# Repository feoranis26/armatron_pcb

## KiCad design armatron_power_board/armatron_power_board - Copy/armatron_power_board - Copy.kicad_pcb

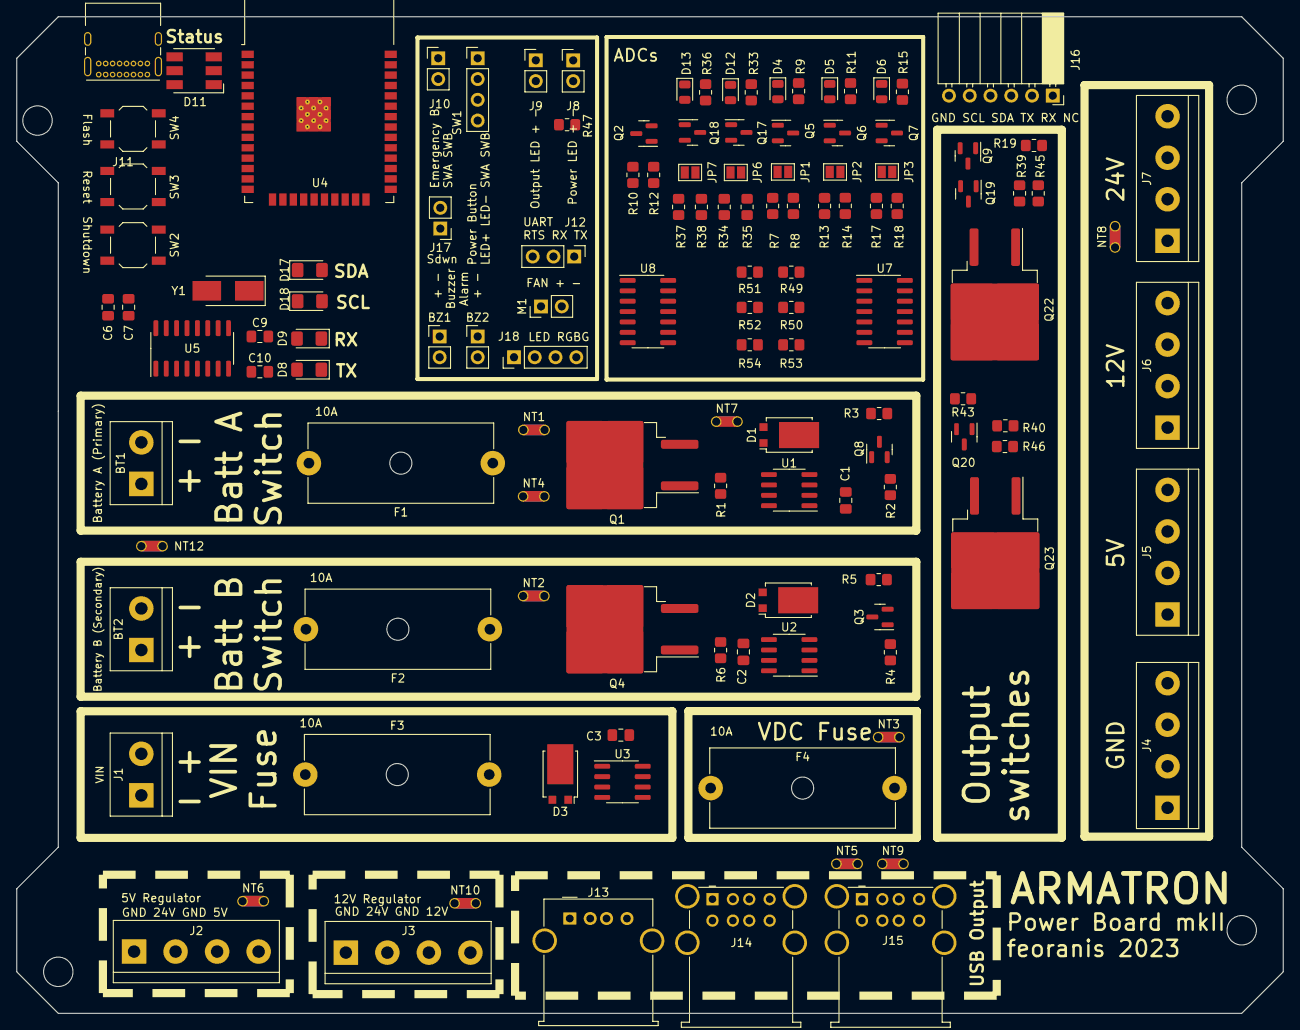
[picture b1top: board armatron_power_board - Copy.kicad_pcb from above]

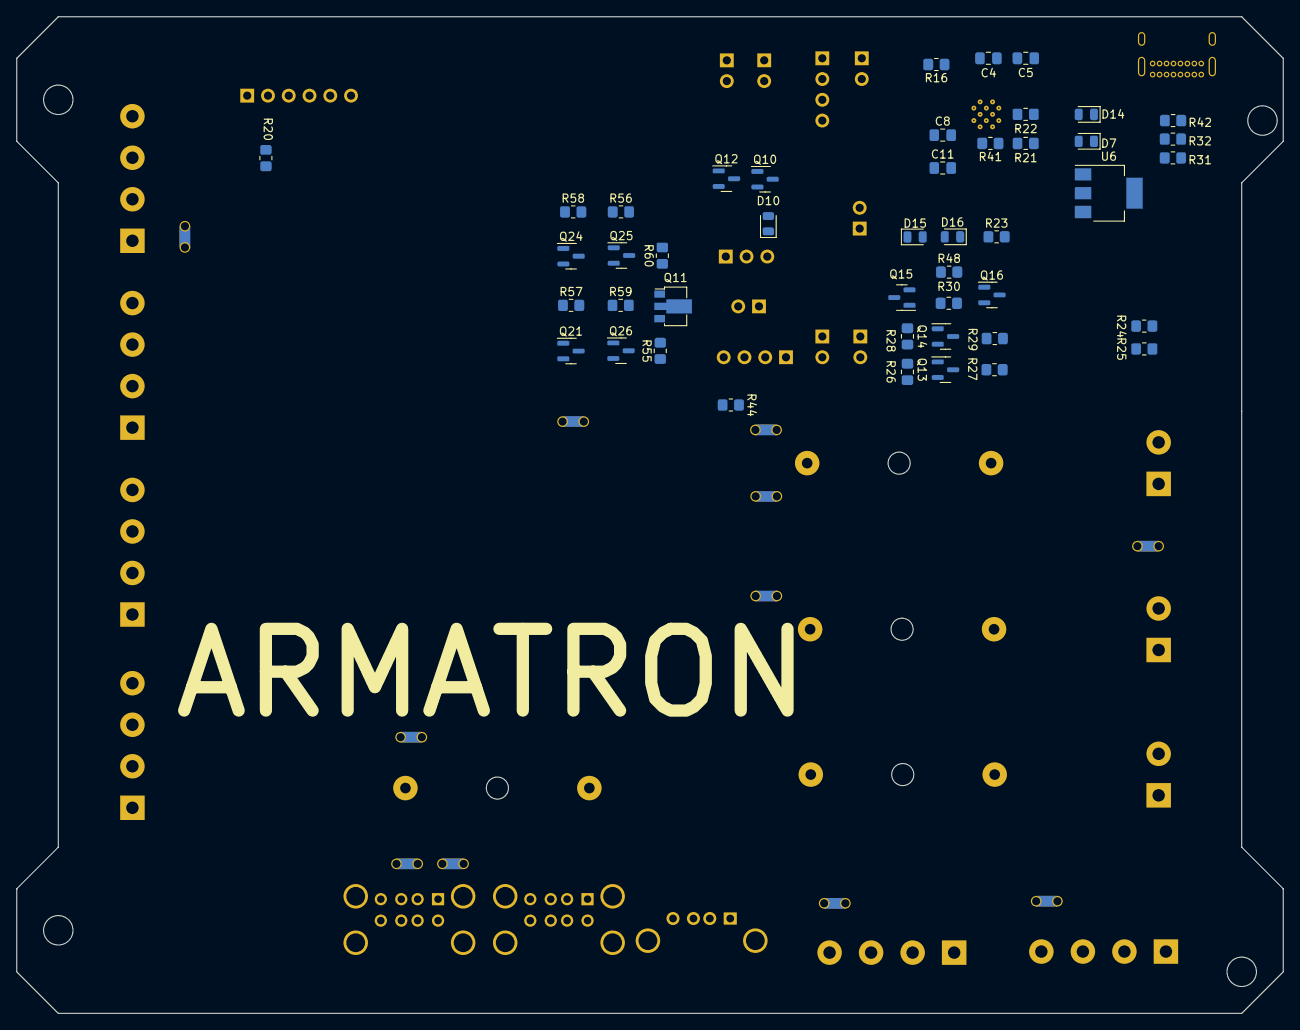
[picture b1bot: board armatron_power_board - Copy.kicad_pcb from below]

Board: 2 copper layers, 154.9 x 121.9 mm, 171 parts (45 on the bottom side), 125 nets, no tracks yet.

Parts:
BT1: Battery A (Primary); TerminalBlock_bornier-2_P5.08mm
BT2: Battery B (Secondary); TerminalBlock_bornier-2_P5.08mm
BZ1, BZ2: Buzzer; PinHeader_1x02_P2.54mm_Vertical
C1, C2, C3: 1n; C_0805_2012Metric_Pad1.18x1.45mm_HandSolder
C4, C7, C8, C11: 100n; C_0805_2012Metric_Pad1.18x1.45mm_HandSolder
C5: 10u; C_0805_2012Metric_Pad1.18x1.45mm_HandSolder
C6: 4.7u; C_0805_2012Metric_Pad1.18x1.45mm_HandSolder
C9, C10: 22pF; C_0805_2012Metric_Pad1.18x1.45mm_HandSolder
D1, D2, D3: D; TO-277B
D4, D5, D6, D7, D10, D12, D13, D14, D15, D16: D; D_0805_2012Metric
D8, D9, D17, D18: LED; LED_1206_3216Metric_Pad1.42x1.75mm_HandSolder
D11: LED_RGB; LED_RGB_5050-6
F1, F2, F3, F4: 10A; Fuseholder_Cylinder-5x20mm_Schurter_0031_8201_Horizontal_Op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
J1: Conn_01x02; TerminalBlock_bornier-2_P5.08mm
J2, J3, J4, J5, J6, J7: Screw_Terminal_01x04; TerminalBlock_bornier-4_P5.08mm
J8, J9, J10, J17: Conn_01x02; PinHeader_1x02_P2.54mm_Vertical
J11: USB_C_Receptacle_USB2.0; USB_C_Receptacle_GCT_USB4085
J12: Conn_01x03_Pin; PinHeader_1x03_P2.54mm_Vertical
J13: USB_A; USB_A_Molex_67643_Horizontal
J14, J15: USB_A_Stacked; USB_A_Wuerth_61400826021_Horizontal_Stacked
J16: Conn_01x06_Socket; PinSocket_1x06_P2.54mm_Horizontal
J18: Conn_01x04_Pin; PinHeader_1x04_P2.54mm_Vertical
JP1, JP2, JP3, JP6, JP7: SolderJumper_2_Open; SolderJumper-2_P1.3mm_Open_Pad1.0x1.5mm
M1: Fan; PinHeader_1x02_P2.54mm_Vertical
NT1, NT2, NT3, NT4, NT5, NT6, NT7, NT8, NT9, NT10, NT12: NetTie_2; NetTie-2_THT_Pad1.0mm
Q1, Q4, Q22, Q23: IRF4905; TO-263-2
Q2, Q3, Q8, Q9, Q10, Q12, Q13, Q14, Q15, Q16, Q19, Q20, Q21, Q24, Q25, Q26: BC817; SOT-23
Q5, Q6, Q7, Q17, Q18: BC807; SOT-23
Q11: BCX56; SOT-89-3
R1, R2, R3, R4, R5, R6, R10, R12, R16, R19, R40, R43, R45, R46: 1K; R_0805_2012Metric_Pad1.20x1.40mm_HandSolder
R7, R13, R17, R34, R37: 220K; R_0805_2012Metric_Pad1.20x1.40mm_HandSolder
R8, R14, R18, R35, R38, R50, R52, R54: 15K; R_0805_2012Metric_Pad1.20x1.40mm_HandSolder
R9, R11, R15, R24, R25, R33, R36: 100K; R_0805_2012Metric_Pad1.20x1.40mm_HandSolder
R20, R21, R22, R23, R26, R28, R30, R39, R41, R44, R47, R48, R55, R56, R59, R60: 10K; R_0805_2012Metric_Pad1.20x1.40mm_HandSolder
R27, R29, R57, R58: 1k; R_0805_2012Metric_Pad1.20x1.40mm_HandSolder
R31, R32, R42: 220R; R_0805_2012Metric_Pad1.20x1.40mm_HandSolder
R49, R51, R53: 22K; R_0805_2012Metric_Pad1.20x1.40mm_HandSolder
SW1: SW_Push_LED; PinHeader_1x04_P2.54mm_Vertical
SW2, SW3, SW4: SW_Push; SW_SPST_TL3342
U1, U2, U3: ACS712xLCTR-20A; SOIC-8_3.9x4.9mm_P1.27mm
U4: ESP32-WROOM-32
U5: CH340G; SOIC-16_3.9x9.9mm_P1.27mm
U6: AMS1117-3.3; SOT-223-3_TabPin2
U7, U8: MCP3428; SOIC-14_3.9x8.7mm_P1.27mm
Y1: 12MHz; Crystal_SMD_5032-2Pin_5.0x3.2mm_HandSoldering

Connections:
5V_Enable: R40.2, U4.31 (IO19)
5V_POWER: J2.4, NT6.2, Q23.2 (D), R46.1
5V_adc: R34.2, R35.1, U8.11 (CH3+)
5V_out: J5.1, J5.2, J5.3, J5.4, J13.1 (VBUS), J14.1 (VBUS1), J14.5 (VBUS2), J15.1 (VBUS1), J15.5 (VBUS2), Q23.3 (S)
12V_POWER: J3.4, J6.1, J6.2, J6.3, J6.4, NT10.1
12V_adc: R37.2, R38.1, U8.13 (CH4+)
24V_Enable: R39.1, U4.36 (IO22)
24V_out: J7.1, J7.2, J7.3, J7.4, NT8.1, Q22.3 (S)
+3.3V: C4.1, C5.1, C6.1, C7.1, D8.1 (K), D9.1 (K), D17.1 (K), D18.1 (K), R16.1, R21.1, R22.1, R23.1, R59.2, R60.2, U4.2 (VDD), U5.4 (V3), U5.16 (VCC), U6.2 (VO), U7.6 (VDD), U8.6 (VDD)
+5V: J16.1, JP6.1 (A), NT6.1, Q17.3 (C), R33.1, U1.8 (VCC), U2.8 (VCC), U3.8 (VCC), U6.3 (VI)
+12V: BZ1.2 (-), BZ2.2 (-), JP7.1 (A), M1.1 (+), NT10.2, Q18.3 (C), R36.1
+VDC: F4.2, J2.2, J3.2, NT3.2, NT5.2, NT9.1, Q22.2 (D), R45.1
ADC_SW_BASE: D4.1 (K), D5.1 (K), D6.1 (K), D12.1 (K), D13.1 (K), R10.1
BATT_A_IN: F1.1, NT1.2, NT4.1, Q1.2 (D), R1.1
BATT_A_LATCH: D1.1 (K), U1.3 (IP-), U1.4 (IP-)
BATT_A_SW: D1.2 (A), NT7.2, Q1.3 (S)
BATT_B_IN: F2.1, NT2.2, Q4.2 (D), R6.1
BATT_B_LATCH: D2.1 (K), U2.3 (IP-), U2.4 (IP-)
BATT_B_SW: D2.2 (A), Q4.3 (S)
D+: J11.A6 (D+), J11.B6 (D+), U5.5 (UD+)
D-: J11.A7 (D-), J11.B7 (D-), U5.6 (UD-)
FLASH_UART: D16.1 (K), Q16.3 (C)
GND: C1.2, C2.2, C3.2, C4.2, C5.2, C6.2, C7.2, C8.2, C11.2, J1.1, J8.2, J9.2, J10.2, J11.A1 (GND), J11.A12 (GND), J11.B1 (GND), J11.B12 (GND), J11.S1 (SHIELD), J13.4 (GND), J13.5 (Shield), J14.4 (GND1), J14.8 (GND2), J14.9 (Shield), J15.4 (GND1), J15.8 (GND2), J15.9 (Shield), J16.6, J17.2, J18.4, NT12.1, Q2.2 (E), Q3.2 (E), Q8.2 (E), Q9.2 (E), Q10.2 (E), Q11.3 (E), Q12.2 (E), Q13.2 (E), Q14.2 (E), Q19.2 (E), Q20.2 (E), Q21.2 (E), Q24.2 (E), Q25.2 (E), Q26.2 (E), R3.2, R5.2, R8.2, R14.2, R18.2, R24.1, R25.2, R31.1, R32.1, R35.2, R38.2, R42.1, R43.2, R50.2, R52.2, R54.2, SW1.3 (K), SW2.2, SW3.2, SW4.2, U1.5 (GND), U2.5 (GND), U3.5 (GND), U4.1 (GND), U4.15 (GND), U4.38 (GND), U4.39 (GND), U5.1 (GND), U6.1 (GND), U7.2 (CH1-), U7.4 (CH2-), U7.5 (VSS), U7.9 (Adr0), U7.10 (Adr1), U7.12 (CH3-), U7.14 (CH4-), U8.2 (CH1-), U8.4 (CH2-), U8.5 (VSS), U8.9 (Adr0), U8.12 (CH3-), U8.14 (CH4-)
unnamed: BT1.1 (+), F1.2
unnamed: BT2.1 (+), F2.2
unnamed: BZ1.1 (+), Q12.3 (C)
unnamed: BZ2.1 (+), Q10.3 (C)
unnamed: D3.2 (A), F3.2
unnamed: D4.2 (A), Q5.1 (B), R9.2
unnamed: D5.2 (A), Q6.1 (B), R11.2
unnamed: D6.2 (A), Q7.1 (B), R15.2
unnamed: D8.2 (A), R27.2
unnamed: D9.2 (A), R29.2
unnamed: D11.4 (BK), R42.2
unnamed: D11.6 (GK), R31.2
unnamed: D11.5 (RK), R32.2
unnamed: D12.2 (A), Q17.1 (B), R33.2
unnamed: D13.2 (A), Q18.1 (B), R36.2
unnamed: D14.1 (K), SW3.1
unnamed: D15.1 (K), SW4.1
unnamed: D17.2 (A), R57.2
unnamed: D18.2 (A), R58.2
unnamed: F4.1, U1.1 (IP+), U1.2 (IP+), U2.1 (IP+), U2.2 (IP+), U3.1 (IP+), U3.2 (IP+)
unnamed: F3.1, J1.2
unnamed: J8.1, NT9.2
unnamed: J9.1, NT8.2
unnamed: J11.A5 (CC1), R24.2
unnamed: J11.B5 (CC2), R25.1
unnamed: JP1.1 (A), NT1.1, Q5.3 (C), R9.1
unnamed: JP1.2 (B), Q5.2 (E), R7.1
unnamed: JP2.1 (A), NT2.1, Q6.3 (C), R11.1
unnamed: JP2.2 (B), Q6.2 (E), R13.1
unnamed: JP3.1 (A), NT3.1, Q7.3 (C), R15.1
unnamed: JP3.2 (B), Q7.2 (E), R17.1
unnamed: JP6.2 (B), Q17.2 (E), R34.1
unnamed: JP7.2 (B), Q18.2 (E), R37.1
unnamed: M1.2 (-), Q11.2 (C)
unnamed: NT4.2, SW1.1
unnamed: NT7.1, SW1.2
unnamed: Q1.1 (G), Q8.3 (C), R1.2
unnamed: Q2.1 (B), R12.1
unnamed: Q2.3 (C), R10.2
unnamed: Q3.1 (B), R4.1, R5.1
unnamed: Q3.3 (C), Q4.1 (G), R6.2
unnamed: Q8.1 (B), R2.1, R3.1
unnamed: Q9.1 (B), R20.2
unnamed: Q9.3 (C), R19.1
unnamed: Q10.1 (B), R44.2
unnamed: Q11.1 (B), R47.2
unnamed: Q12.1 (B), R41.2
unnamed: Q13.1 (B), R26.2
unnamed: Q13.3 (C), R27.1
unnamed: Q14.1 (B), R28.2
unnamed: Q14.3 (C), R29.1
unnamed: Q15.1 (B), R30.2
unnamed: Q16.1 (B), R48.2
unnamed: Q19.1 (B), R19.2, R39.2
unnamed: Q19.3 (C), Q22.1 (G), R45.2
unnamed: Q20.1 (B), R40.1, R43.1
unnamed: Q20.3 (C), Q23.1 (G), R46.2
unnamed: Q21.1 (B), Q26.3 (C), R59.1
unnamed: Q21.3 (C), R57.1
unnamed: Q24.1 (B), Q25.3 (C), R60.1
unnamed: Q24.3 (C), R58.1
unnamed: Q25.1 (B), R56.2
unnamed: Q26.1 (B), R55.2
unnamed: NT5.1, SW1.4 (A)
unnamed: C1.1, U1.6 (FILTER)
unnamed: C2.1, U2.6 (FILTER)
unnamed: C3.1, U3.6 (FILTER)
unnamed: C9.1, U5.7 (XI), Y1.1
unnamed: C10.1, U5.8 (XO), Y1.2
PIN_ADC_BATT_A: R7.2, R8.1, U7.1 (CH1+)
PIN_ADC_BATT_B: R13.2, R14.1, U7.3 (CH2+)
PIN_ADC_ENA: R12.2, U4.30 (IO18)
PIN_ADC_VIN: R17.2, R18.1, U7.11 (CH3+)
PIN_ALARM: R44.1, U4.9 (IO33)
PIN_BATT_A_SENSE: R49.1, U1.7 (VIOUT), U7.13 (CH4+)
PIN_BATT_A_SENSE_ADC: R49.2, R50.1
PIN_BATT_B_SENSE: R51.1, U2.7 (VIOUT), U8.1 (CH1+)
PIN_BATT_B_SENSE_ADC: R51.2, R52.1
PIN_BUZZER: R41.1, U4.8 (IO32)
PIN_EmergencyButton: J10.1, R16.2, R20.1, U4.37 (IO23)
PIN_FLASH: C11.1, D15.2 (A), D16.2 (A), R23.2, U4.25 (IO0)
PIN_Fan: R47.1, U4.26 (IO4)
PIN_RESET: C8.1, D7.2 (A), D10.2 (A), D14.2 (A), R22.2, U4.3 (EN)
PIN_RGB_B: D11.3 (BA), J18.3, U4.10 (IO25)
PIN_RGB_G: D11.1 (GA), J18.2, U4.13 (IO14)
PIN_RGB_R: D11.2 (RA), J18.1, U4.16 (IO13)
PIN_Sdwn_Btn: J17.1, R21.2, SW2.1, U4.33 (IO21)
PIN_VBATT_A_ENBL: R2.2, U4.27 (IO16)
PIN_VBATT_B_ENBL: R4.2, U4.28 (IO17)
PIN_VIN_SENSE: R53.1, U3.7 (VIOUT), U8.3 (CH2+)
PIN_VIN_SENSE_ADC: R53.2, R54.1
POWER_GND: BT1.2 (-), BT2.2 (-), J2.1, J2.3, J3.1, J3.3, J4.1, J4.2, J4.3, J4.4, NT12.2
RESET_Header: D10.1 (K), J12.3
RESET_UART: D7.1 (K), Q15.3 (C)
RX: J12.2, J16.2, R28.1, U4.34 (RXD0/IO3), U5.2 (TXD)
RXD: J12.1, J16.3, R26.1, U4.35 (TXD0/IO1), U5.3 (RXD)
SCL: J16.5, R55.1, U4.12 (IO27), U7.8 (SCL), U8.8 (SCL)
SDA: J16.4, R56.1, U4.11 (IO26), U7.7 (SDA), U8.7 (SDA)
VBUS: J11.A4 (VBUS), J11.A9 (VBUS), J11.B4 (VBUS), J11.B9 (VBUS)
VIN: D3.1 (K), U3.3 (IP-), U3.4 (IP-)
nDTR: Q16.2 (E), R30.1, U5.13 (~DTR)
nRTS: Q15.2 (E), R48.1, U5.14 (~RTS)
